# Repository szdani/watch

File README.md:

# Binary Watch

## Project Structure
- `pcb`: KiCAD based PCB & Schematic
- `3dmodel`: CADQuery based 3D Model for printing/cnc
- `frimeware`: Code for the STM32WB - Uploading is progress

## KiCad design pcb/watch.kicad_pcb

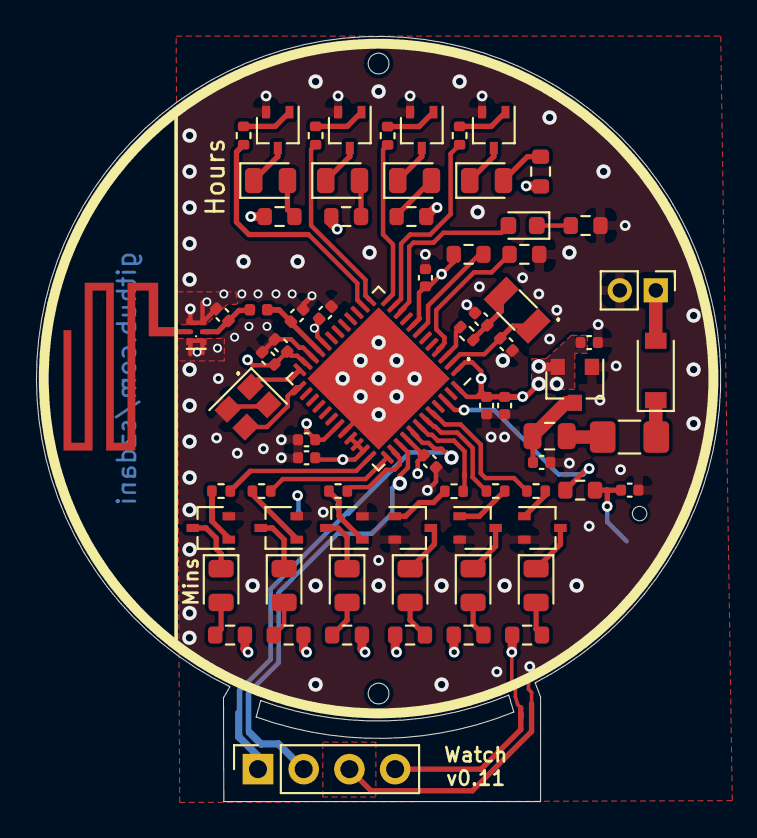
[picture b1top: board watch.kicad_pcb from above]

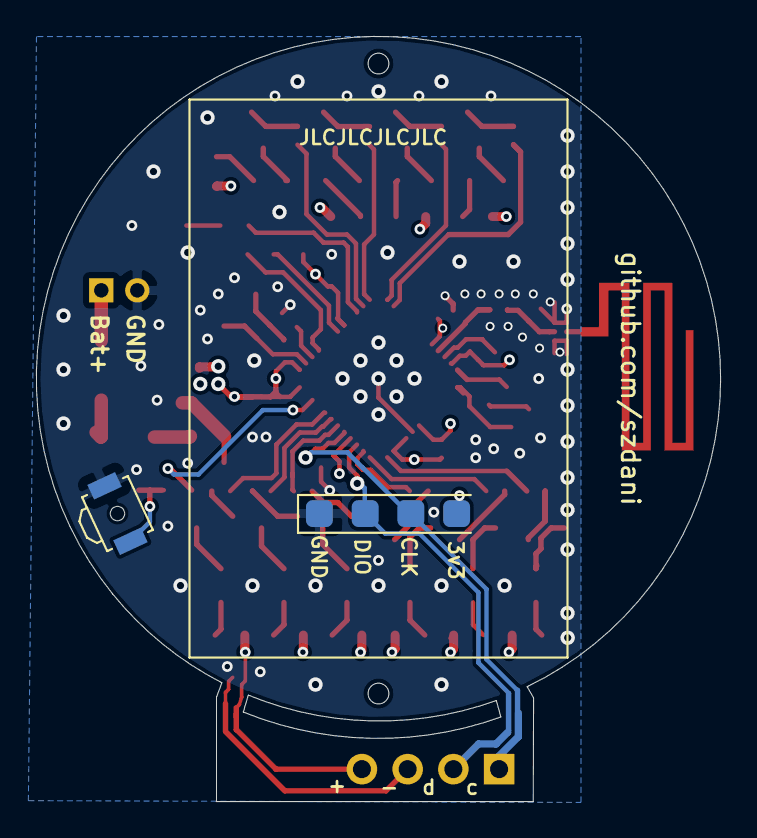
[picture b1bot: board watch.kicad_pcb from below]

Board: 4 copper layers, 38.0 x 42.5 mm, 78 parts (2 on the bottom side), 62 nets.

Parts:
AE1: Antenna; STM32_PCB_Antenna_Mirrored
C1: 4.7uF; C_0402_1005Metric
C2, C4, C6, C8, C9, C13, C15, C16: 100nF; C_0402_1005Metric
C3, C5: C_Small; C_0402_1005Metric
C7, C10: 1uF; C_0402_1005Metric
C11: 0.8pF; C_0402_1005Metric
C12: 0.3pF; C_0402_1005Metric
C14: 100pF; C_0402_1005Metric
D1, D2, D3, D4, D5, D6, D7, D8, D9, D11: LED_Blue; LED_0805_2012Metric
D10: LED_Red; LED_0603_1608Metric
D12: B5819W; D_SOD-123
F1: 200mA; Fuse_1206_3216Metric_Pad1.42x1.75mm_HandSolder
FB1: 100 @ 100 MHz; C_0805_2012Metric
H1: SMD_1; SMD_Tooling_Hole
H2: SMD2; SMD_Tooling_Hole
J1: Conn_01x04_Female; Connector_PCB
J2: Batt; PinHeader_1x02_P2.00mm_Vertical
J3: Conn_01x04_Female; PinSocket_1x04_P2.54mm_Vertical
L1: 2.7nH; L_0402_1005Metric
Q2, Q3, Q4, Q5, Q6, Q7, Q8, Q9, Q10, Q11: VBK162K; SOT-323_SC-70
R1: 100K; R_0603_1608Metric
R2, R24: 10K; R_0603_1608Metric
R3, R4, R5, R6, R11, R13, R16, R17, R20, R21: 160; R_0402_1005Metric
R7, R8, R9, R10, R14, R15, R18, R19, R22, R23: 20 Ohm; R_0603_1608Metric
R12: 2k2; R_0603_1608Metric
R25: 5.1k; R_0402_1005Metric
SW1: Omron Electronics B3U-3000PM-B; SW_SPST_B3U-3000P-B
U1: STM32WB30CEU5A; QFN-48-1EP_7x7mm_P0.5mm_EP5.6x5.6mm
U2: XC6206PxxxMR; SOT-23
U3: SLFL18-2R450G-02TF; SLFL18
Y1: 32.768KHZ; Crystal_SMD_3215-2Pin_3.2x1.5mm
Y2: 32MHz; Crystal_SMD_2520-4Pin_2.5x2.0mm

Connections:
+BATT: D12.2, J2.1
ANTENNA: C11.1, L1.2, U1.21
BOOT0: R2.2, U1.4
BUTTON: R24.2, U1.46
GND: C1.2, C2.2, C3.2, C4.2, C5.2, C6.2, C7.2, C8.2, C9.2, C10.1, C11.2, C12.2, C13.2, C14.2, C15.2, C16.2, J1.4, J2.2, J3.3, Q2.2, Q3.2, Q4.2, Q5.2, Q6.2, Q7.2, Q8.2, Q9.2, Q10.2, Q11.2, R2.1, R12.2, SW1.2, U1.22, U1.32, U2.1, U3.1, U3.3, U3.4, U3.6, Y2.2, Y2.4
LED_H_1: R20.2, U1.11
LED_H_2: R5.2, U1.12
LED_H_4: R21.2, U1.13
LED_H_8: R3.2, U1.14
LED_M_1: R17.2, U1.44
LED_M_2: R13.2, U1.43
LED_M_4: R6.2, U1.42
LED_M_8: R16.2, U1.38
LED_M_16: R11.2, U1.37
LED_M_32: R4.2, U1.36
LED_NOTIF: D10.2, U1.10
LF_OSC_IN: C3.1, U1.2, Y1.1
LF_OSC_OUT: R25.1, U1.3
unnamed: AE1.1, U3.5
unnamed: C5.1, R25.2, Y1.2
unnamed: C7.1, FB1.1, U2.3
unnamed: C12.1, L1.1, U3.2
unnamed: C15.1, R24.1, SW1.1
unnamed: D1.1, Q4.3
unnamed: D1.2, R7.2
unnamed: D2.1, Q2.3
unnamed: D2.2, R8.2
unnamed: D3.1, Q5.3
unnamed: D3.2, R9.2
unnamed: D4.1, Q3.3
unnamed: D4.2, R10.2
unnamed: D5.1, Q10.3
unnamed: D5.2, R22.2
unnamed: D6.1, Q6.3
unnamed: D6.2, R14.2
unnamed: D7.1, Q8.3
unnamed: D7.2, R23.2
unnamed: D8.1, Q7.3
unnamed: D8.2, R15.2
unnamed: D9.1, Q9.3
unnamed: D9.2, R18.2
unnamed: D10.1, R12.1
unnamed: D11.1, Q11.3
unnamed: D11.2, R19.2
unnamed: D12.1, F1.1
unnamed: F1.2, FB1.2
unnamed: Q2.1, R4.1
unnamed: Q3.1, R6.1
unnamed: Q4.1, R3.1
unnamed: Q5.1, R5.1
unnamed: Q6.1, R11.1
unnamed: Q7.1, R13.1
unnamed: Q8.1, R21.1
unnamed: Q9.1, R16.1
unnamed: Q10.1, R20.1
unnamed: Q11.1, R17.1
unnamed: R1.2, U1.7
RF_OSC_IN: U1.25, Y2.3
RF_OSC_OUT: U1.24, Y2.1
SWCLK: J1.2, J3.1, U1.41
SWDIO: J1.3, J3.2, U1.39
VDD: C1.1, C2.1, C4.1, C6.1, C8.1, C9.1, C10.2, C13.1, C14.1, C16.1, J1.1, J3.4, R1.1, R7.1, R8.1, R9.1, R10.1, R14.1, R15.1, R18.1, R19.1, R22.1, R23.1, U1.1, U1.8, U1.20, U1.23, U1.31, U1.33, U1.34, U1.35, U1.40, U1.48, U2.2

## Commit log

2021-04-10 PCB design (kicad)
2021-04-10 3D Model
2021-04-10 screenshots: pcb+case
2021-04-10 Udpate readme with screenshot
2021-04-10 3d model with top-bottom connection
2021-04-10 3D model cap tolerance
2021-04-10 main README
2021-04-11 3d model code cleanup
2021-04-11 PCB - fix reverse polarity protection with a diode
2021-04-12 3D model update
    - reduce body size to 40mm
    reduce strap size to 19mm
    - new watchface holder
2021-04-12 3D model screenshot update
